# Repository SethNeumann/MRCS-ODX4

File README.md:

# REPO NAME: MRCS-ODX4
## License: Creative Commons Attribution-NonCommercial-ShareAlike

The ODX-4 has been updated to version 2.0. Based on customer feedback, and our design and installation experience, the changes were made to provide more efficient and flexible physical layout of some components.  Rev 2.0 boards are 100% backward compatible with older versions. No software changes are needed.

- Board size 2.7" x 3.9" 69 x 100 mm

- The board can be split into two DCC sections by cutting the SPLIT pad jumper trace.

- DCC Bus connections are 5 mm screw terminal blocks.

- A power, Ground, and Detector connection is provided on a 6-position .100 (2.54 mm) screw terminal block.

The ODX4 provides an economical and convenient mounting for up to four cpOD-M detectors or DCC_OD "Optimized Detectors."  0.156 screw terminals are provided for 12V power, ground, DCC, and four logic outputs, one for each detector position.  DCC_OD are available as boards from JLC Enterprises.

The ODX4 mounts in our DIN-Rail snap track.

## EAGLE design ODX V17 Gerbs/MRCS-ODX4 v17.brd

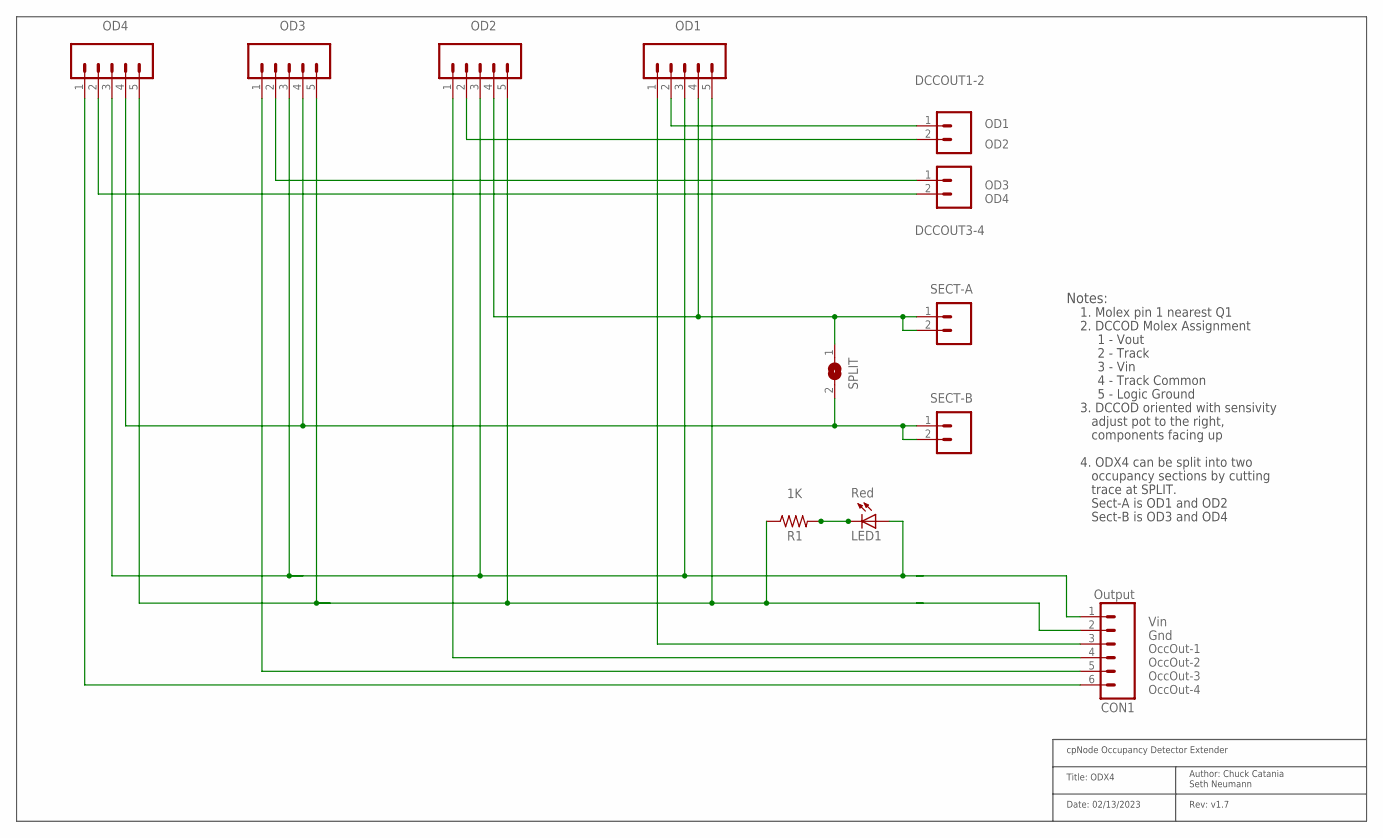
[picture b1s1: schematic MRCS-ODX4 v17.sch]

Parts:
CON1: Output; MOLEX-1X6_LOCK
DCCOUT1-2, DCCOUT3-4: CONNECTOR-M025MM-LOCK; SCREWTERMINAL-5MM-2
LED1: Red; LED3MM
OD1, OD2, OD3, OD4: M05PTH_LONGPADS; 1X05_LONGPADS
R1: 1K; AXIAL-0.4-RES
SECT-A: M025MM; SCREWTERMINAL-5MM-2
SECT-B: M025MM; SCREWTERMINAL-5MM-2
SPLIT: SJW

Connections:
GND: CON1.2, OD1.5, OD2.5, OD3.5, OD4.5, R1.P$1 (1)
unnamed: DCCOUT3-4.2 (B), OD4.2
unnamed: CON1.3, OD1.1
unnamed: DCCOUT1-2.1 (A), OD1.2
unnamed: DCCOUT1-2.2 (B), OD2.2
unnamed: LED1.K (C), R1.P$2 (2)
unnamed: CON1.6, OD4.1
unnamed: OD3.4, OD4.4, SECT-B.1, SECT-B.2, SPLIT.2
unnamed: OD1.4, OD2.4, SECT-A.1, SECT-A.2, SPLIT.1
unnamed: CON1.4, OD2.1
unnamed: DCCOUT3-4.1 (A), OD3.2
unnamed: CON1.5, OD3.1
VIN: CON1.1, LED1.A, OD1.3, OD2.3, OD3.3, OD4.3

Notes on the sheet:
Rev: v1.7
Date: 02/13/2023
Title: ODX4
cpNode Occupancy Detector Extender
Author: Chuck Catania Seth Neumann
Vin
Gnd
OccOut-1
OccOut-2
OccOut-3
5 - Logic Ground
4 - Track Common
3 - Vin
2 - Track
1 - Vout
2. DCCOD Molex Assignment
Notes:
3. DCCOD oriented with sensivity
adjust pot to the right,
components facing up
OD1
OD2
OD3
OD4
OccOut-4
1. Molex pin 1 nearest Q1
4. ODX4 can be split into two
occupancy sections by cutting
trace at SPLIT.
Sect-A is OD1 and OD2
Sect-B is OD3 and OD4

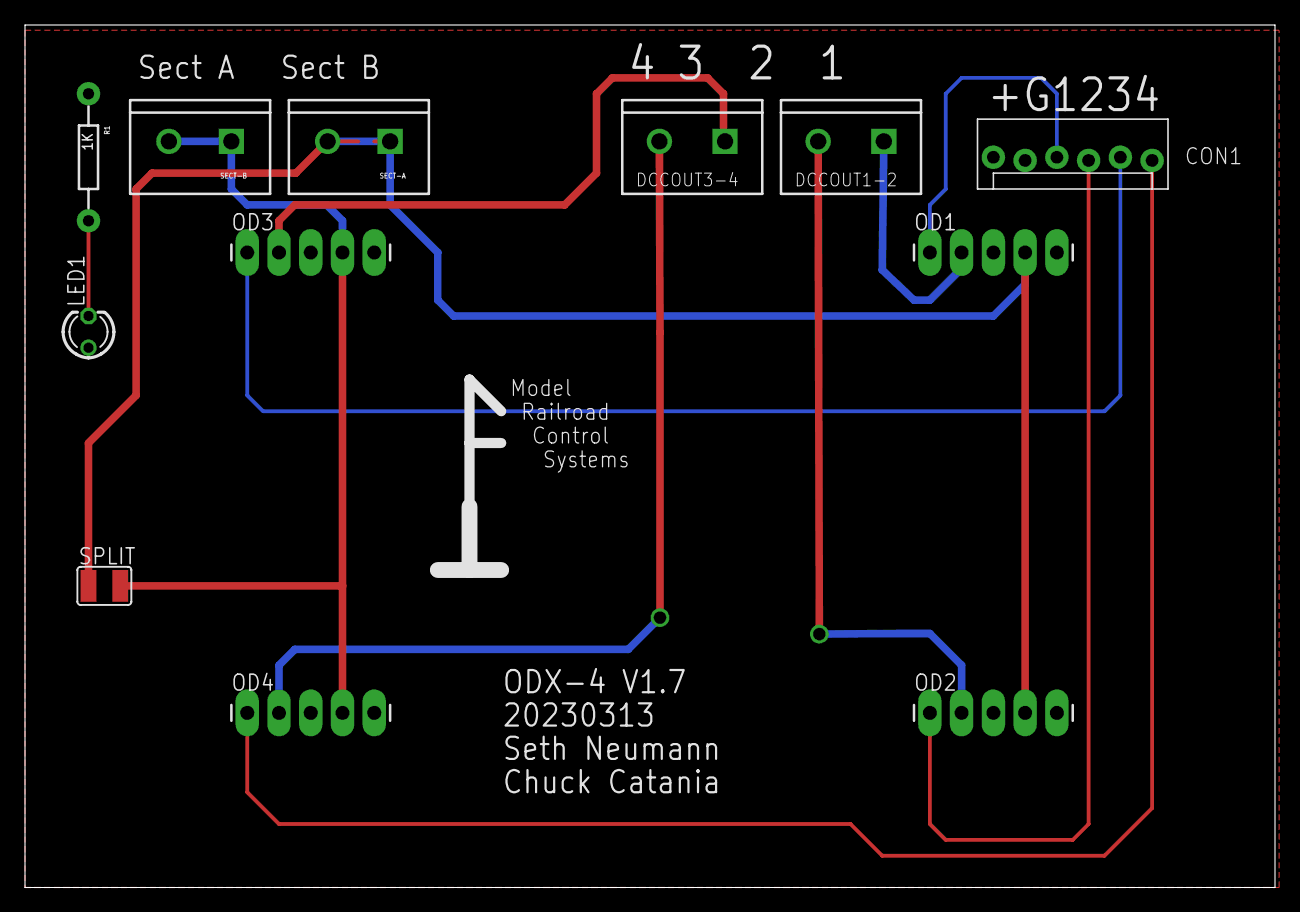
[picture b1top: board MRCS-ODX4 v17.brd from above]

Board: 2 copper layers, 100.0 x 69.0 mm, 13 parts (0 on the bottom side), 13 nets.

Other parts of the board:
U$1: MRCS-LOGO

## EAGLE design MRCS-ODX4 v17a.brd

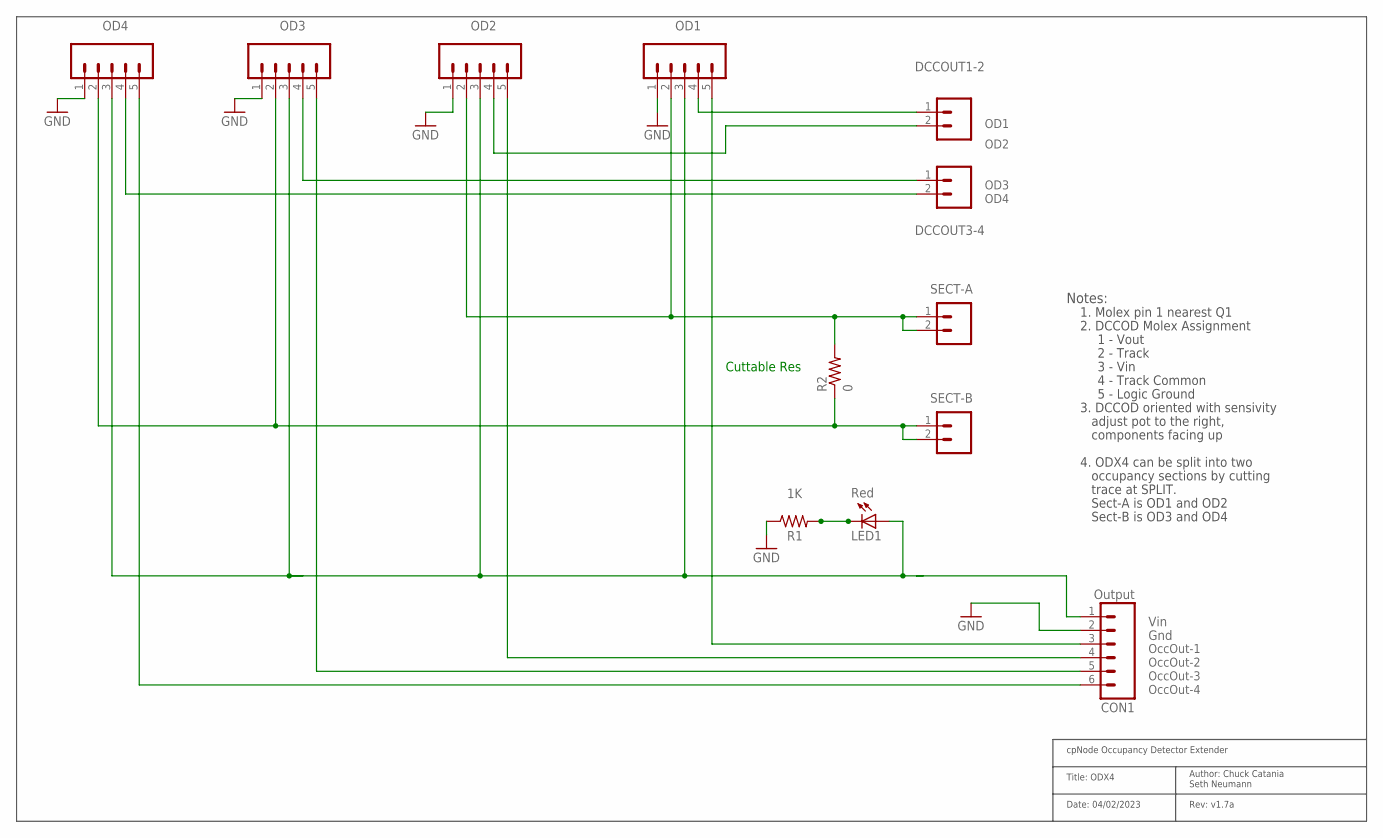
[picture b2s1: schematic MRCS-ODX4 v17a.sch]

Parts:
CON1: Output; MOLEX-1X6_LOCK
DCCOUT1-2, DCCOUT3-4: CONNECTOR-M025MM-LOCK; SCREWTERMINAL-5MM-2
LED1: Red; LED3MM
OD1, OD2, OD3, OD4: CONNECTOR-M051.56; KK-156-5
R1: 1K; AXIAL-0.4-RES
R2: 0; CUT-R
SECT-A: M025MM; SCREWTERMINAL-5MM-2
SECT-B: M025MM; SCREWTERMINAL-5MM-2

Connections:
GND: CON1.2, OD1.1, OD2.1, OD3.1, OD4.1, R1.P$1 (1)
unnamed: CON1.6, OD4.5
unnamed: LED1.K (C), R1.P$2 (2)
OCCOUT1: CON1.3, OD1.5
OCCOUT2: CON1.4, OD2.5
OCCOUT3: CON1.5, OD3.5
SECT-A: OD1.2, OD2.2, R2.P1 (2), SECT-A.1, SECT-A.2
SECT-B: OD3.2, OD4.2, R2.P2 (1), SECT-B.1, SECT-B.2
TO1: DCCOUT1-2.1 (A), OD1.4
TO2: DCCOUT1-2.2 (B), OD2.4
TO3: DCCOUT3-4.1 (A), OD3.4
TO4: DCCOUT3-4.2 (B), OD4.4
VIN: CON1.1, LED1.A, OD1.3, OD2.3, OD3.3, OD4.3

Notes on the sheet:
Rev: v1.7a
Date: 04/02/2023
Title: ODX4
cpNode Occupancy Detector Extender
Author: Chuck Catania Seth Neumann
Vin
Gnd
OccOut-1
OccOut-2
OccOut-3
5 - Logic Ground
4 - Track Common
3 - Vin
2 - Track
1 - Vout
2. DCCOD Molex Assignment
Notes:
3. DCCOD oriented with sensivity
adjust pot to the right,
components facing up
OD1
OD2
OD3
OD4
OccOut-4
1. Molex pin 1 nearest Q1
4. ODX4 can be split into two
occupancy sections by cutting
trace at SPLIT.
Sect-A is OD1 and OD2
Sect-B is OD3 and OD4
Cuttable Res

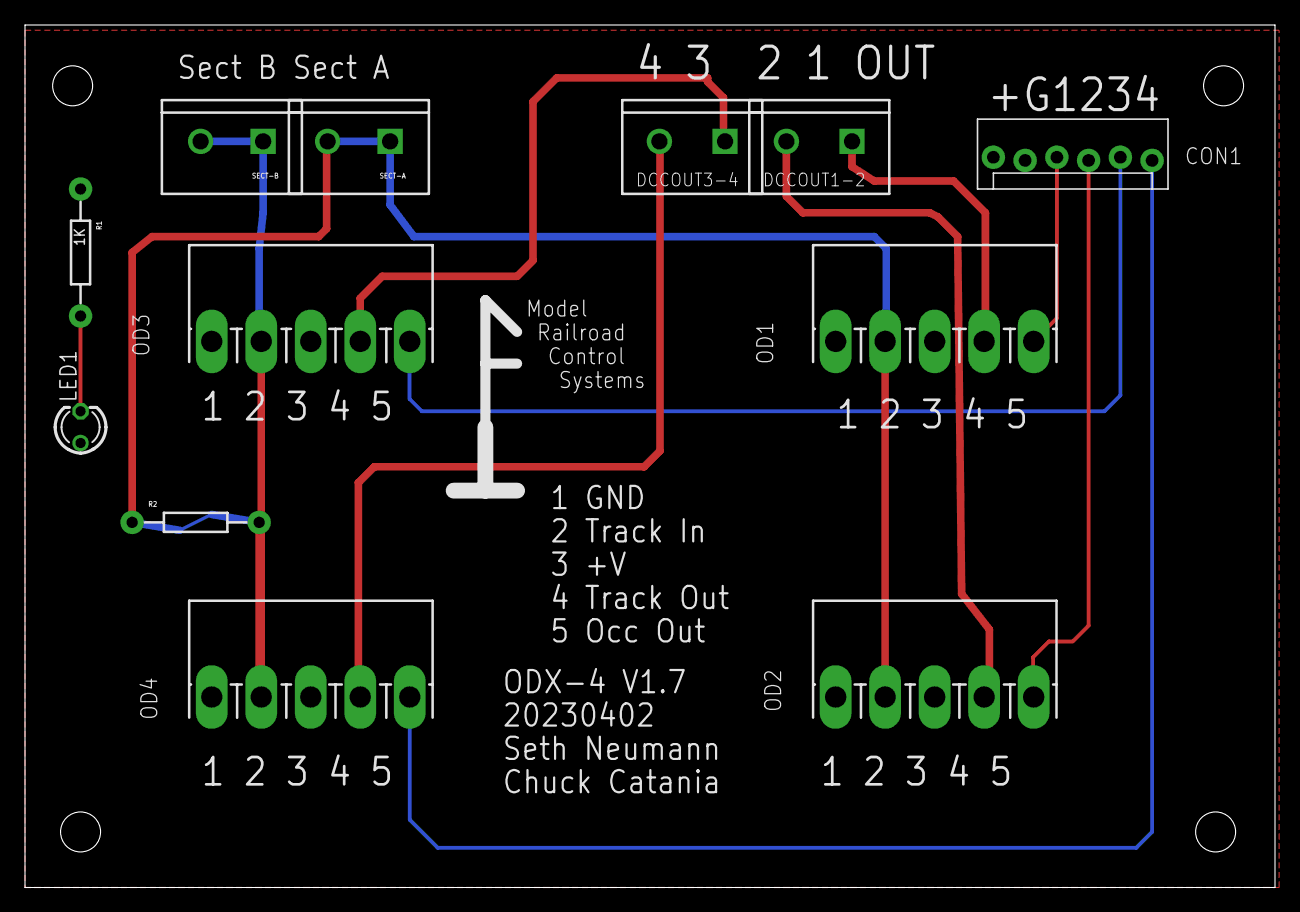
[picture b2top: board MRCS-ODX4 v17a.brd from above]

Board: 2 copper layers, 100.0 x 69.0 mm, 15 parts (0 on the bottom side), 13 nets.

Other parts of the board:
U$1: MRCS-LOGO
U$2: MRCSLOGOBTM
U$3: CA-PROP65WARNING

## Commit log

2021-01-25 intial commit
    intial commit
2021-01-25 initial commit
    initial commit
2021-01-25 changed name
    changed name
2021-01-26 migrated existing ODX v16 files
    migrated existing ODX v16 files
2021-01-26 Create MRCS-ODX4 Schematic.pdf
    added pdf schematic for users who don't use EAGLE
2023-04-03 V1.7
    moved 5mm connectors, added power LED
2023-04-03 V1.7
    moved 5mm connectors, updated labels, added power LEDs

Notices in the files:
parts and their libraries:
SparkFun-Connectors: Licensing: CC v3.0 Share-Alike You are welcome to use this library for commercial purposes.
